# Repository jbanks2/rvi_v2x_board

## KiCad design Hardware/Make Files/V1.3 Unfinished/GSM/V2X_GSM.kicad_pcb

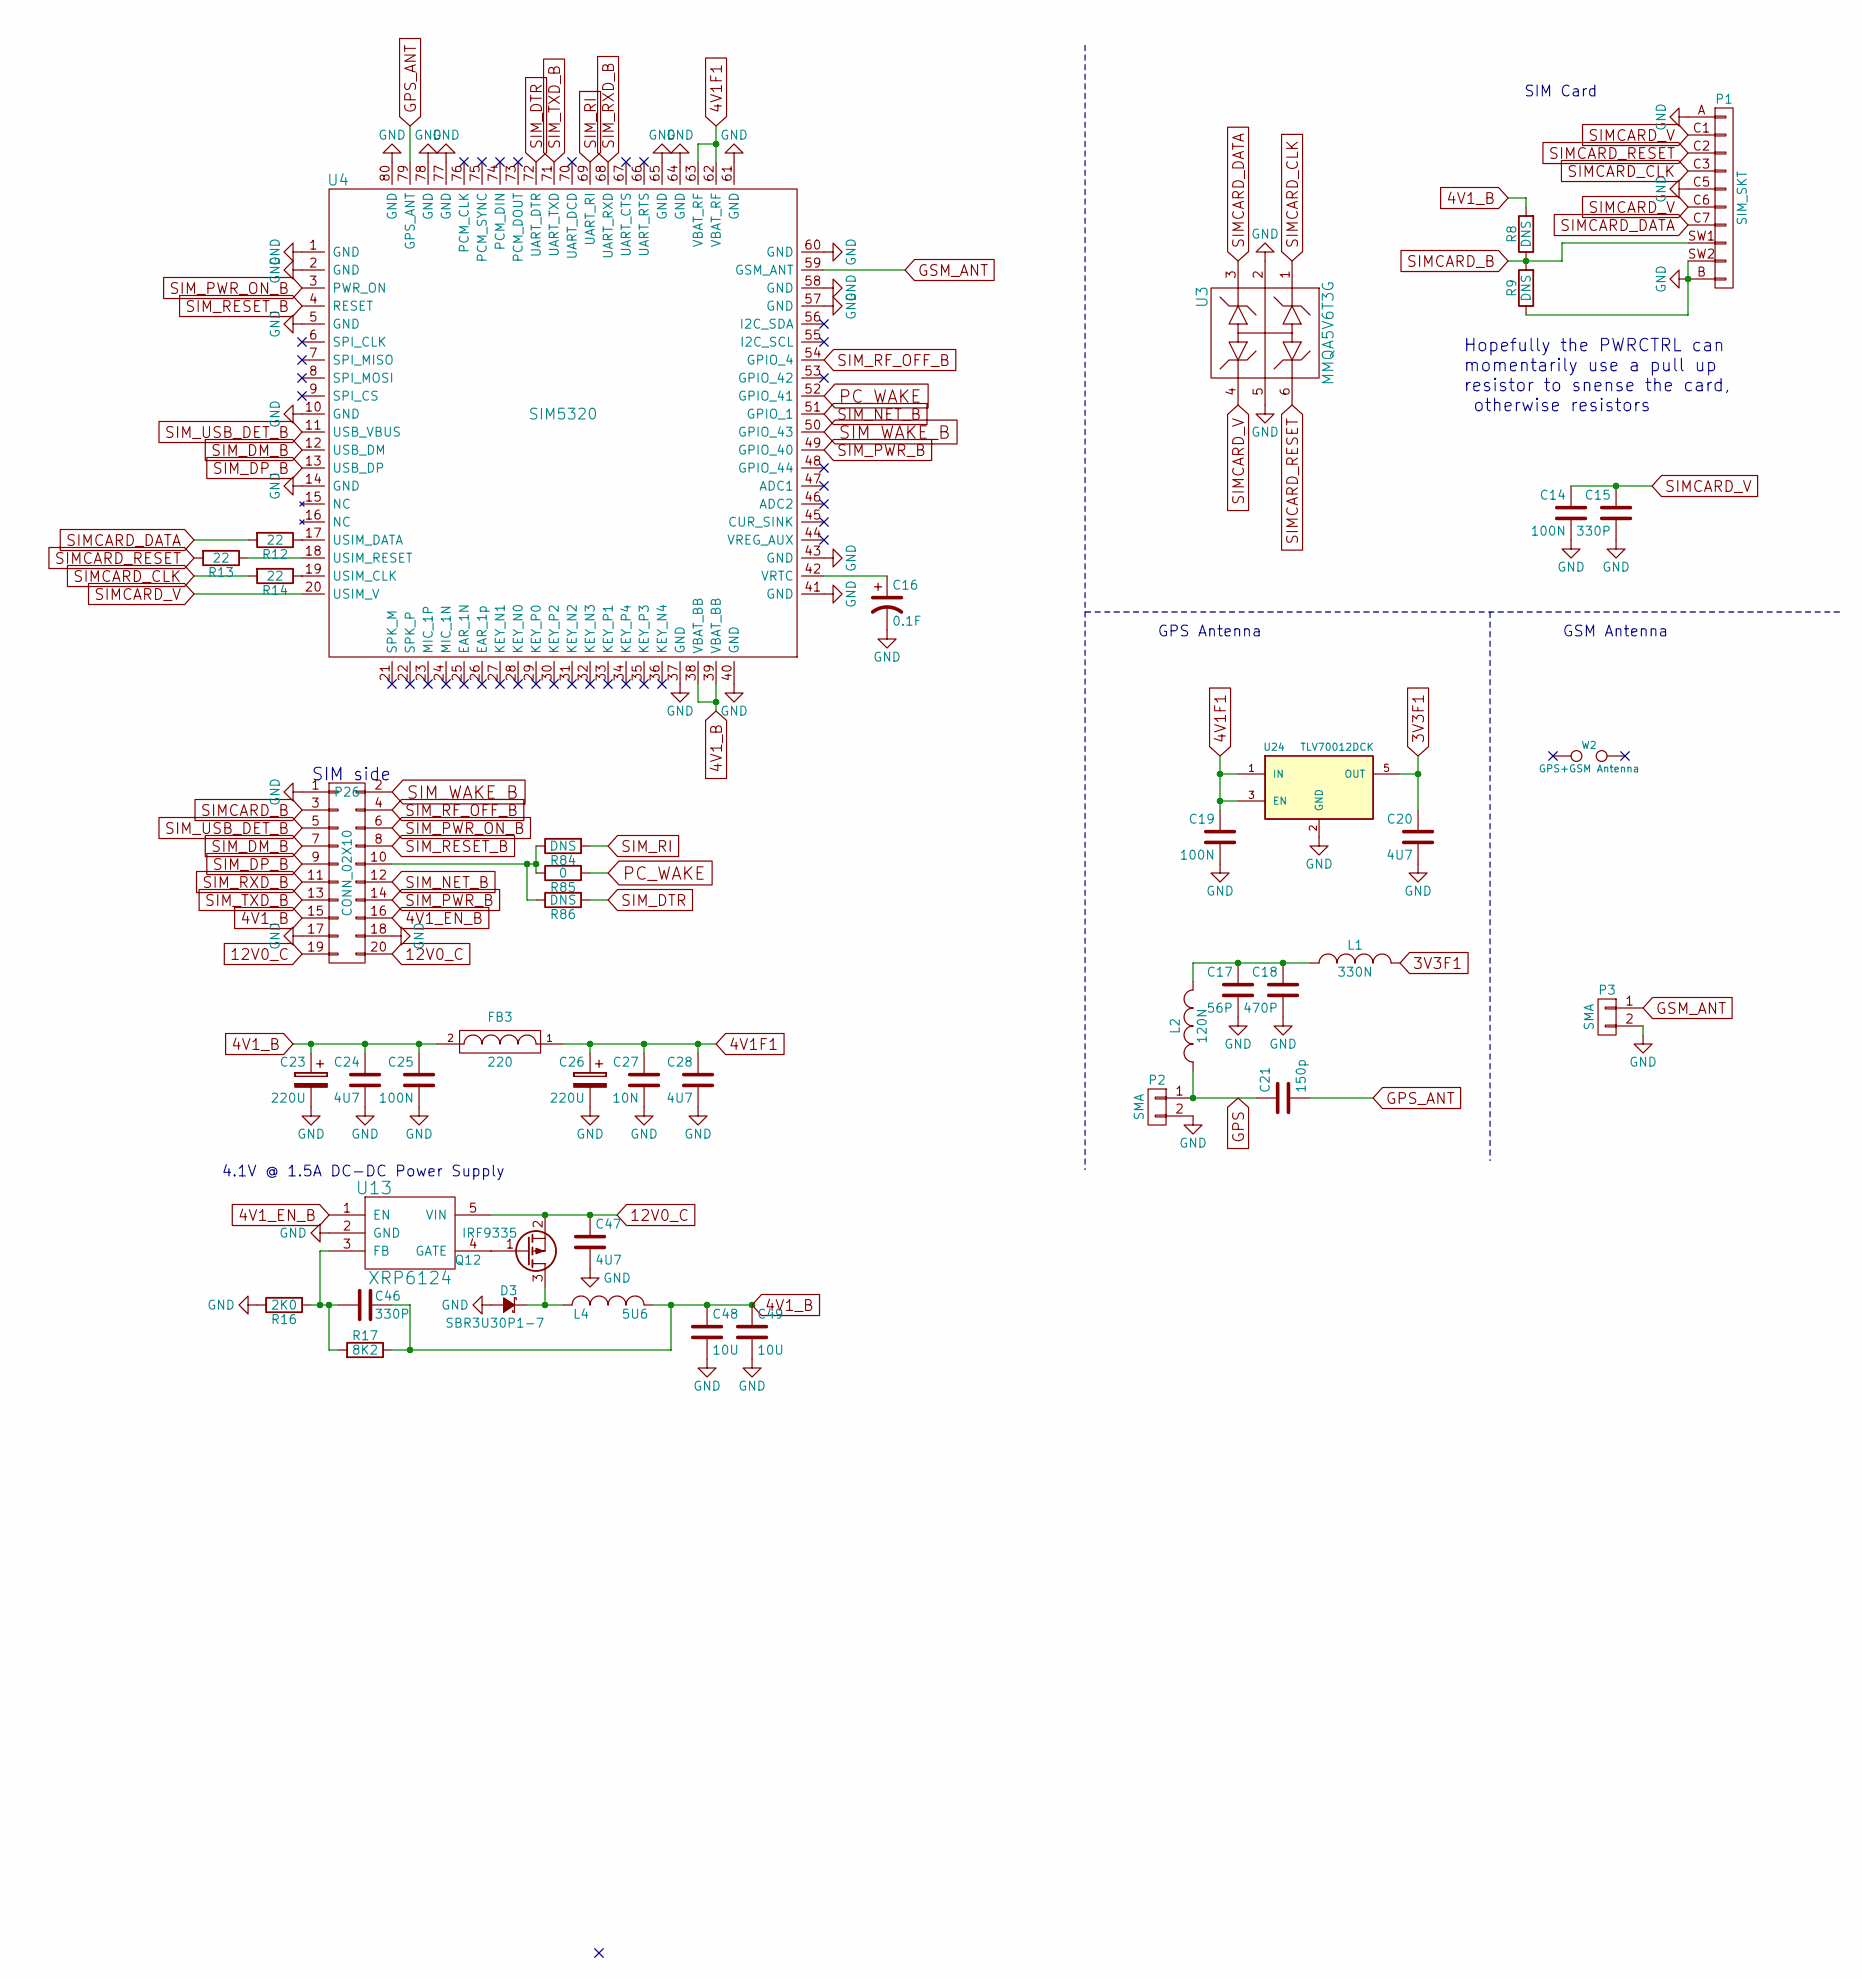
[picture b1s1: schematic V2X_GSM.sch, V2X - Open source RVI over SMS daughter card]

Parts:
C14, C19, C25: 100N; C_0603_SM
C15, C46: 330P; C_0603_SM
C16: 0.1F; C_Radial_D12.5_L25_P5; Mouser PN 504-KR-5R5C104-R
C17: 56P; C_0603_SM
C18: 470P; C_0603_SM
C20, C24, C28, C47: 4U7; C_0805_SM
C21: 150p; C_0603_SM
C23, C26: 220U; c_elec_6.3x5.8
C27: 10N; C_0603_SM
C48, C49: 10U; C_1206_SM
D3: SBR3U30P1-7; SOD-123
FB3: 220; R_0603_sm
L1: 330N; C_0603_SM
L2: 120N; C_0603_SM
L4: 5U6; 4.5x4.5mm_Ind
P1: SIM_SKT; 47553-1001
P2, P3: SMA; SMA-RA_142-0701-801
P26: CONN_02X10; FFC-1MMx20
Q12: IRF9335; SOIC-8_MOS
R8, R9, R84, R86: DNS; R_0603_sm
R12, R13, R14: 22; R_0603_sm
R16: 2K0; R_0603_sm
R17: 8K2; R_0603_sm
R85: 0; R_0603_sm
U3: MMQA5V6T3G; SOT-23-6
U4: SIM5320
U13: XRP6124; SOT-23-5
U24: TLV70012DCK; SOT-23-5
W2: GPS+GSM Antenna

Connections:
3V3F1: C20.1, L1.1, U24.5 (OUT)
4V1F1: C19.1, C26.1, C27.1, C28.1, FB3.1, U4.62 (VBAT_RF), U4.63 (VBAT_RF), U24.1 (IN), U24.3 (EN)
4V1_B: C23.1, C24.1, C25.1, C46.1, C48.1, C49.1, FB3.2, L4.2, P26.15, R8.2, R17.1, U4.38 (VBAT_BB), U4.39 (VBAT_BB)
4V1_EN_B: P26.16, U13.1 (EN)
12V0_C: C47.1, P26.19, P26.20, Q12.2 (S), U13.5 (VIN)
GND: C14.2, C15.2, C16.2, C17.2, C18.2, C19.2, C20.2, C23.2, C24.2, C25.2, C26.2, C27.2, C28.2, C47.2, C48.2, C49.2, D3.2 (A), P1.A, P1.B, P1.C5, P1.SW2, P2.2, P3.2, P26.1, P26.17, P26.18, R9.1, R16.1, U3.2 (K), U3.5 (K2), U4.1 (GND), U4.2 (GND), U4.5 (GND), U4.10 (GND), U4.14 (GND), U4.37 (GND), U4.40 (GND), U4.41 (GND), U4.43 (GND), U4.57 (GND), U4.58 (GND), U4.60 (GND), U4.61 (GND), U4.64 (GND), U4.65 (GND), U4.77 (GND), U4.78 (GND), U4.80 (GND), U13.2 (GND), U24.2 (GND)
GPS: C21.1, L2.1, P2.1
GPS_ANT: C21.2, U4.79 (GPS_ANT)
GSM_ANT: P3.1, U4.59 (GSM_ANT)
unnamed: C16.1, U4.42 (VRTC)
unnamed: C17.1, C18.1, L1.2, L2.2
unnamed: C46.2, R16.2, R17.2, U13.3 (FB)
unnamed: D3.1 (K), L4.1, Q12.3 (D)
unnamed: P26.10, R84.1, R85.1, R86.1
unnamed: Q12.1 (G), U13.4 (GATE)
unnamed: R12.1, U4.17 (USIM_DATA)
unnamed: R13.1, U4.18 (USIM_RESET)
unnamed: R14.1, U4.19 (USIM_CLK)
PC_WAKE: R85.2, U4.52 (GPIO_41)
SIMCARD_B: P1.SW1, P26.3, R8.1, R9.2
SIMCARD_CLK: P1.C3, R14.2, U3.1 (A1)
SIMCARD_DATA: P1.C7, R12.2, U3.3 (A2)
SIMCARD_RESET: P1.C2, R13.2, U3.6 (A4)
SIMCARD_V: C14.1, C15.1, P1.C1, P1.C6, U3.4 (A4), U4.20 (USIM_V)
SIM_DM_B: P26.7, U4.12 (USB_DM)
SIM_DP_B: P26.9, U4.13 (USB_DP)
SIM_DTR: R86.2, U4.72 (UART_DTR)
SIM_NET_B: P26.12, U4.51 (GPIO_1)
SIM_PWR_B: P26.14, U4.49 (GPIO_40)
SIM_PWR_ON_B: P26.6, U4.3 (PWR_ON)
SIM_RESET_B: P26.8, U4.4 (RESET)
SIM_RF_OFF_B: P26.4, U4.54 (GPIO_4)
SIM_RI: R84.2, U4.69 (UART_RI)
SIM_RXD_B: P26.11, U4.68 (UART_RXD)
SIM_TXD_B: P26.13, U4.71 (UART_TXD)
SIM_USB_DET_B: P26.5, U4.11 (USB_VBUS)
SIM_WAKE_B: P26.2, U4.50 (GPIO_43)

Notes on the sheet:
SIM Card
GPS Antenna
GSM Antenna
Hopefully the PWRCTRL can momentarily use a pull up resistor to snense the card, otherwise resistors
SIM side
4.1V @ 1.5A DC-DC Power Supply

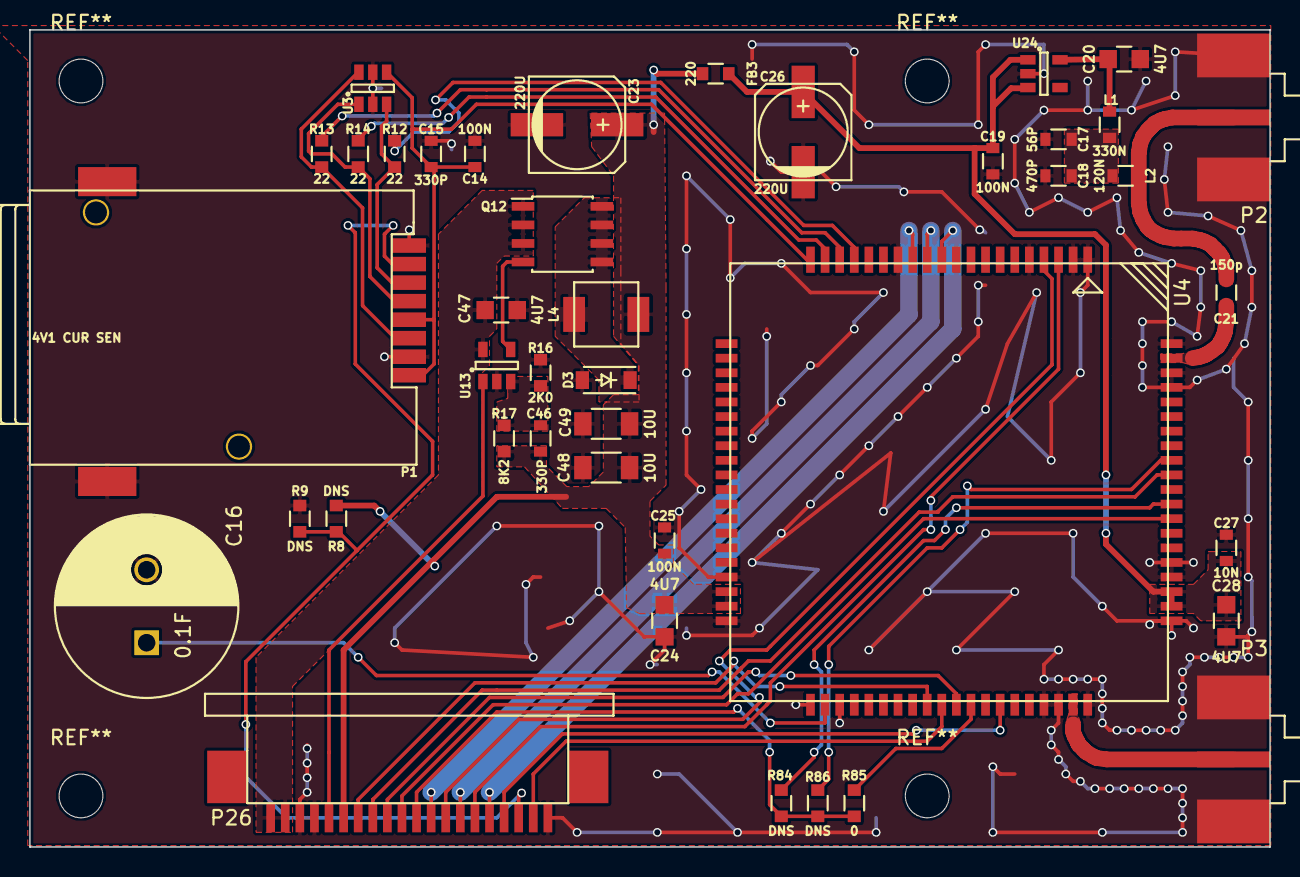
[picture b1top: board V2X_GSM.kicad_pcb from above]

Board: 2 copper layers, 85.0 x 56.0 mm, 42 parts (0 on the bottom side), 37 nets.

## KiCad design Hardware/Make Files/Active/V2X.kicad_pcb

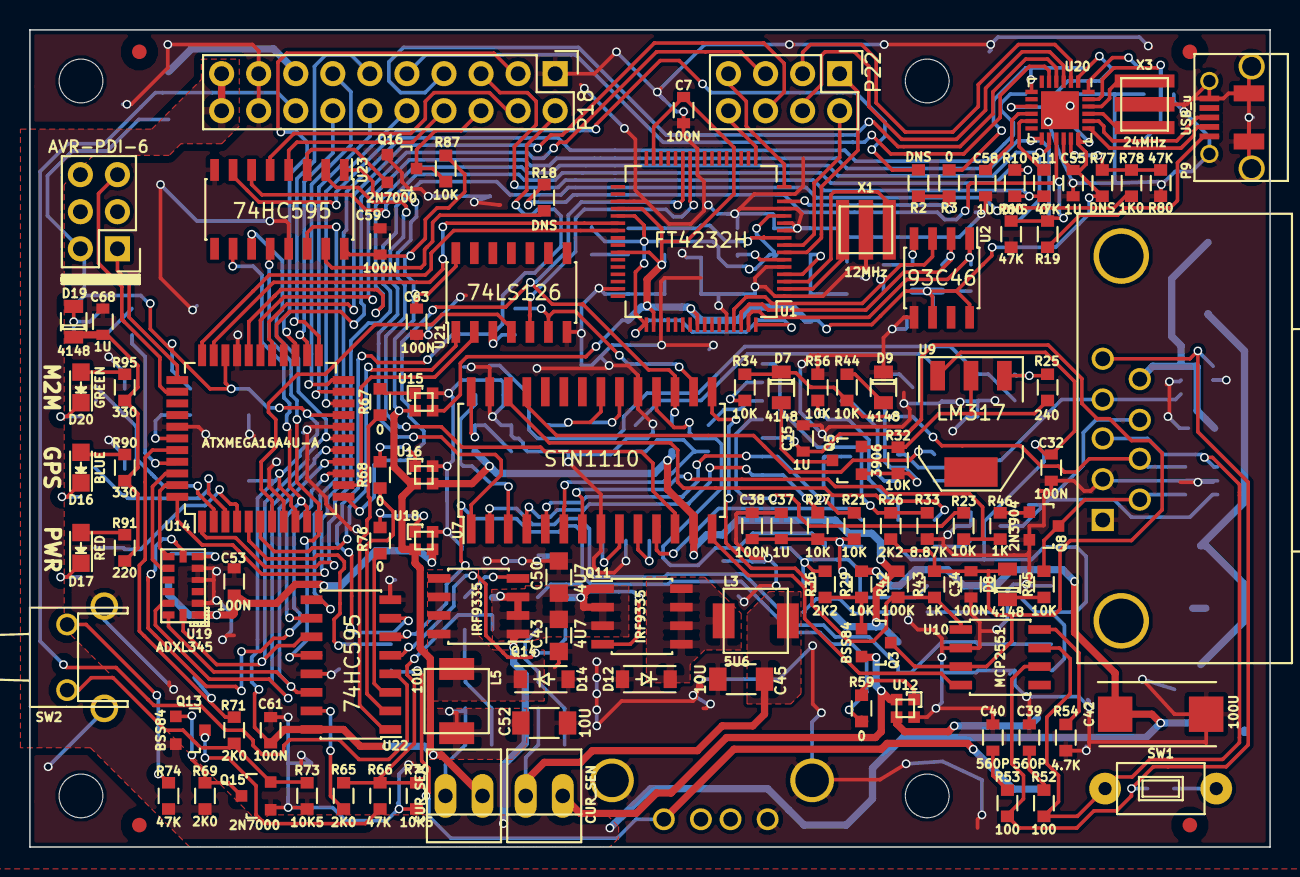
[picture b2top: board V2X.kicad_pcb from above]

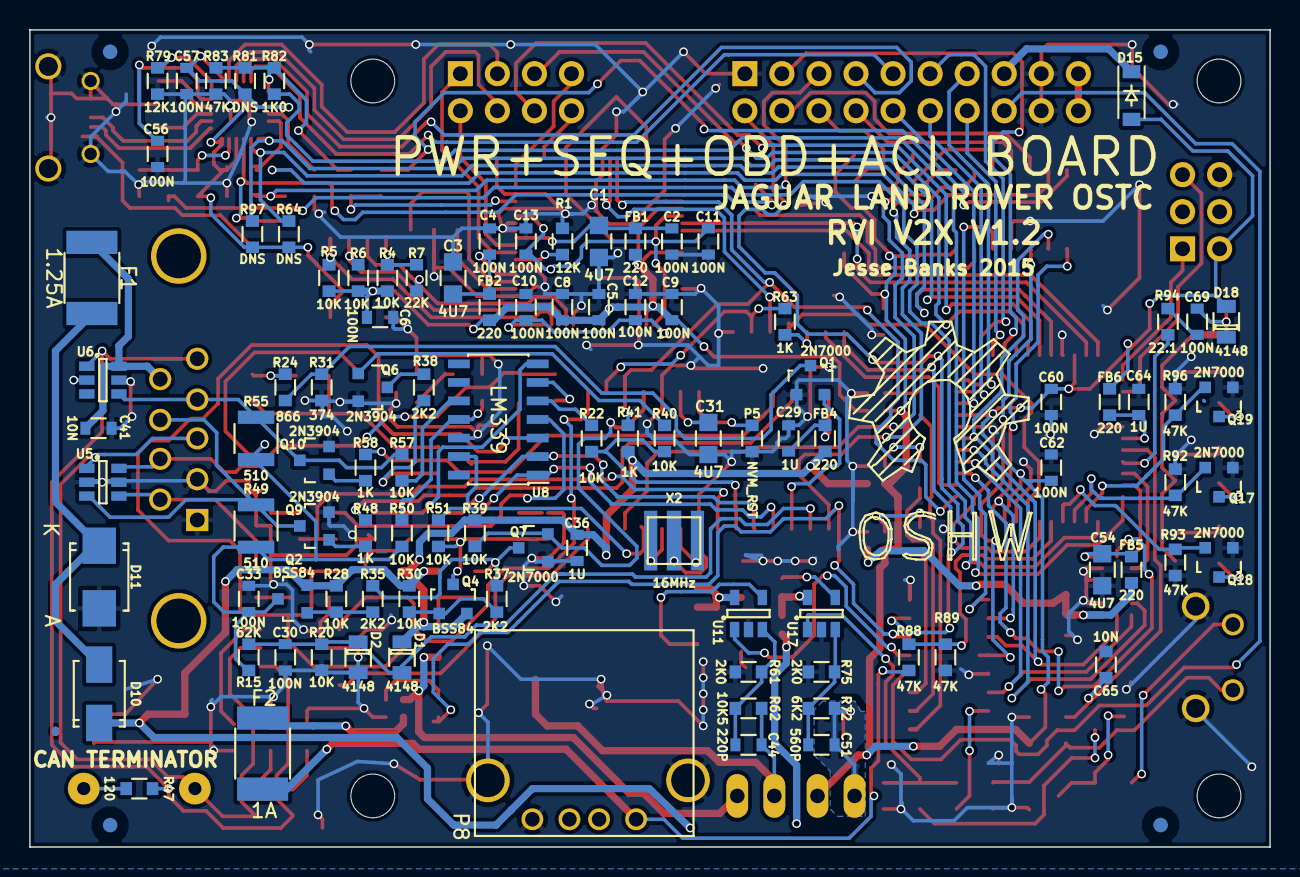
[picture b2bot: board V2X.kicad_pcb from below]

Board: 2 copper layers, 85.0 x 56.0 mm, 223 parts (106 on the bottom side), 179 nets.

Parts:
C1, C3, C31, C43, C50, C54: 4U7; C_0805_SM
C2, C4, C5, C6, C7, C8, C9, C10, C11, C12, C13, C30, C32, C33, C34, C38, C53, C56, C57, C59, C60, C61, C62, C63, C69: 100N; C_0603_SM
C29, C35, C36, C37, C55, C58, C64, C68: 1U; C_0603_SM
C39, C40, C51: 560P; C_0603_SM
C41: 10N; C_0603_SM
C42: 100U; TantalC_SizeD_EIA-7343_Reflow
C44: 220P; C_0603_SM
C45, C52: 10U; C_1206_SM
C65: 10N; R_0603_sm
CON1: AVR-PDI-6; Pin_Header_Straight_2x03
D1, D2, D7, D8, D9, D18, D19: 4148; Diode_0805_12_SM
D10: B320A-13-F; SMA_Standard
D11: SMBJ16A; SMB_Standard
D12, D14: SBR3U30P1-7; SOD-123
D15: MMSZ4678T1G; SOD-123
D16: BLUE; LED-0805-SM
D17: RED; LED-0805-SM
D20: GREEN; LED-0805-SM
F1: 1.25A; R_1812
F2: 1A; R_1812
FB1, FB2, FB4, FB5, FB6: 220; R_0603_sm
J1: DB9; D09P13B4PA00LF
L3: 5U6; 4.5x4.5mm_Ind
L5: 10U; 4.5x4.5mm_Ind
P5: NVM_RST; R_0603_sm
P6: Board Mount 1; MountingHole_3mm
P7: Ficudial1; Fiducial_1mm_Dia_2.54mm_Outer_CopperTop
P8: USB_A
P9: USB_u; USB_Micro-B-DX4R005JJ2R1800
P10: Board Mount 2; MountingHole_3mm
P11: Ficudial2; Fiducial_1mm_Dia_2.54mm_Outer_CopperTop
P12: Board Mount 3; MountingHole_3mm
P13: Ficudial3; Fiducial_1mm_Dia_2.54mm_Outer_CopperTop
P15: Board Mount 4; MountingHole_3mm
P16: Ficudial4; Fiducial_1mm_Dia_2.54mm_Outer_CopperTop
P17, P19: CUR_SEN; PINHEAD1-2
P18: CONN_02X08; Pin_Header_Straight_2x10
P20: Jumper 1; Fiducial_1mm_Dia_2.54mm_Outer_CopperTop
P21: Jumper 2; Fiducial_1mm_Dia_2.54mm_Outer_CopperTop
P22: CONN_02X04; Pin_Header_Straight_2x04
P23: Jumper 3; Fiducial_1mm_Dia_2.54mm_Outer_CopperTop
P24: Jumper 4; Fiducial_1mm_Dia_2.54mm_Outer_CopperTop
Q1, Q7, Q15, Q16, Q17, Q18, Q19: 2N7000; SOT_23_123
Q2, Q3, Q4, Q13: BSS84; SOT_23_123
Q5: 3906; SOT_23_123
Q6, Q8, Q9, Q10: 2N3904; SOT_23_123
Q11, Q14: IRF9335; SOIC-8_MOS
R1, R79: 12K; R_0603_sm
R2, R10, R18, R64, R77, R81, R97: DNS; R_0603_sm
R3, R11, R59, R67, R68, R76: 0; R_0603_sm
R4, R5, R6, R20, R21, R22, R23, R27, R28, R29, R30, R32, R34, R39, R40, R44, R45, R50, R51, R56, R57, R87: 10K; R_0603_sm
R7: 22K; R_0603_sm
R15: 62K; R_0603_sm
R19, R60, R66, R74, R80, R83, R88, R89, R92, R93, R96: 47K; R_0603_sm
R24: 866; R_0603_sm
R25: 240; R_0603_sm
R26, R35, R36, R37, R38: 2K2; R_0603_sm
R31: 374; R_0603_sm
R33: 8.87K; R_0603_sm
R41, R43, R46, R48, R58, R63: 1K; R_0603_sm
R42: 100K; R_0603_sm
R47: 120; R_0603_sm
R49, R55: 510; R_1210_SM
R52, R53: 100; R_0603_sm
R54: 4.7K; R_0603_sm
R61, R65, R69, R71, R75: 2K0; R_0603_sm
R62, R70, R73: 10K5; R_0603_sm
R72: 6K2; R_0603_sm
R78, R82: 1K0; R_0603_sm
R90, R95: 330; R_0603_sm
R91: 220; R_0603_sm
R94: 22.1; R_0603_sm
SW1: SPST; SW_SPST_A6TN_TH
SW2: SW_PUSH; PTS645VK58-2-LFS
U1: FT4232H; LQFP-64_10x10mm_Pitch0.5mm
U2: 93C46; SOIC-8_3.9x4.9mm_Pitch1.27mm
U5, U6: ESDAxxSC6; SOT-23-6
U7: STN1110; SOIC-28_7.5x17.9mm_Pitch1.27mm
U8: LM339; SOIC-14_3.9x8.7mm_Pitch1.27mm
U9: LM317; SOT-223
U10: MCP2551; SOIC-8_3.9x4.9mm_Pitch1.27mm
U11, U17: XRP6124; SOT-23-5
U12, U15, U16, U18: SLG59M; STDFN-4
U14: ATXMEGA16A4U-A; TQFP-44_10x10mm_Pitch0.8mm
U19: ADXL345; LGA-14_5x3mm
U20: USB2242; QFN-24-1EP_4x4mm_Pitch0.5mm
U21: 74LS126; SOIC-14_3.9x8.7mm_Pitch1.27mm
U22, U23: 74HC595; SOIC-16_3.9x9.9mm_Pitch1.27mm
X1: 12MHz; AWSCR
X2: 16MHz; AWSCR
X3: 24MHz; AWSCR

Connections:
3V3_A: C59.1, C60.1, C61.1, C62.1, C63.1, CON1.2, D15.2, D18.2, FB6.1, P19.1, R87.2, U14.9, U14.19, U14.31, U15.2, U16.2, U18.2, U21.14, U22.16, U23.16
3V3_B: C5.1, C6.1, C7.1, C8.1, C9.1, C55.1, C57.1, FB1.1, FB2.1, R4.2, R5.1, R6.1, R64.2, R77.2, R81.2, R97.2, U1.20, U1.31, U1.36, U1.42, U1.50, U1.56, U2.6, U2.8, U15.3, U20.1, U20.9, U20.16, U20.18
3V3_B_EN: R67.1, U22.1
3V3_C: C36.1, D1.1, FB4.1, Q4.2, R39.1, R41.1, R42.1, U7.13, U16.3
3V3_C_EN: R68.1, U22.2
3V3_D: C53.1, FB5.1, U18.3, U19.1
3V3_D_EN: R76.1, U22.3
3V3_E: C68.1, D19.1, R90.2, R91.2, R95.2
3V3_EN: R65.1, U22.15
3V3_F: C64.1, FB6.2, U14.39
4V1_A: D15.1, P18.15
4V1_EN: P18.16, U22.4
5V0_A: P17.1, Q3.2, U12.2
5V0_B: F2.1, U12.3
5V0_B_EN: R59.1, U22.6
5V0_B_OUT: F2.2, P8.1, R88.2
5V0_EN: U11.1, U22.5
5V0_HOST: P9.1, R19.1
12V0_A: C41.1, F1.1, J1.9, U6.6
12V0_B: C42.1, C43.1, C50.1, D10.1, P18.19, P18.20, Q2.2, Q11.2, Q13.2, Q14.2, R28.1, R29.1, R30.1, R69.1, R74.1, U11.5, U17.5
ACCEL_RXD: U1.38, U14.32
ACCEL_TXD: U1.39, U14.33
ACL_INT1: U14.43, U19.8
ACL_INT2: U14.42, U19.9
BAT_SAMPLE: C30.1, D1.2, D2.1, R15.2, R20.1, U7.2
BUTTON: C65.2, R71.2, U14.40
CAN_3.3V_SW: C37.1, C38.1, Q4.3, R21.1, R27.1, R51.1
CAN_5V_SW: C34.1, C35.1, D8.2, Q3.3, R26.1, R43.1, U8.3, U10.3
CAN_12V_SW: C32.1, C33.1, Q2.3, R15.1, R49.2, R50.1, R55.2, U9.3
CAN_BUF_FTDI: U14.7, U21.4
CAN_BUF_SEQ: U14.6, U21.1
CAN_CLK: U7.9, X2.1
CAN_CLKN: U7.10, X2.2
CAN_H: J1.3, R52.1, SW1.1, U5.1, U10.7
CAN_L: J1.5, R47.1, R53.1, U6.1, U10.6
CAN_POWERDOWN: Q7.2, R39.2, U7.18
CAN_RX: U7.14, U10.4
CAN_RXD: R63.2, U7.16, U21.6
CAN_RXD_FTDI: U1.26, U21.5
CAN_RXD_SEQ: U14.13, U21.2
CAN_TX: R42.2, R43.2, U7.15, U10.1
CAN_TXD: R41.2, U1.27, U7.17, U14.12
EECLK: R6.2, U1.62, U2.2
EECS: R5.2, U1.63, U2.1
EEDATA: R7.2, U1.61, U2.3
FT1V8: C10.1, C11.1, C12.1, C13.1, U1.12, U1.37, U1.49, U1.64
FT3V3PHY: C3.1, C4.1, FB2.2, U1.4
FT3V3PLL: C1.1, C2.1, FB1.2, U1.9
FTDI_DM: P22.1, U1.7
FTDI_DP: P22.2, U1.8
FT_CLK: U1.2, X1.2
FT_CLKN: U1.3, X1.1
GND: C1.2, C2.2, C3.2, C4.2, C5.2, C6.2, C7.2, C8.2, C9.2, C10.2, C11.2, C12.2, C13.2, C29.2, C30.2, C31.2, C32.2, C33.2, C34.2, C35.2, C36.2, C37.2, C38.2, C39.2, C40.2, C41.2, C42.2, C43.2, C45.2, C50.2, C52.2, C53.2, C54.2, C55.2, C56.2, C57.2, C58.2, C59.2, C60.2, C61.2, C62.2, C63.2, C64.2, C65.1, C68.2, CON1.6, D2.2, D9.1, D11.2, D12.2, D14.2, J1.1, J1.2, P5.2, P8.4, P8.5, P9.5, P9.6, P18.1, P18.17, P18.18, Q1.1, Q6.2, Q7.1, Q8.2, Q9.2, Q10.2, Q15.1, Q16.1, Q17.1, Q18.1, Q19.1, R1.2, R20.2, R31.1, R33.1, R54.2, R56.2, R60.2, R61.1, R70.1, R73.1, R75.2, R79.1, R80.2, R83.1, R89.1, R92.1, R93.1, R96.1, SW2.S, U1.1, U1.5, U1.10, U1.11, U1.13, U1.15, U1.25, U1.35, U1.47, U1.51, U1.60, U2.5, U5.2, U5.5, U6.2, U6.5, U7.8, U7.19, U7.27, U8.12, U10.2, U11.2, U12.4, U14.8, U14.18, U14.30, U14.38, U15.4, U16.4, U17.2, U18.4, U19.2, U19.4, U19.5, U20.25, U21.7, U22.8, U22.13, U23.8, U23.13, X1.3, X2.3, X3.3
HOST_SC: R88.1, R89.2, U14.5
HUB_CLK: U20.22, X3.2
HUB_CLKN: U20.21, X3.1
HUB_DM: P9.2, U20.19
HUB_DP: P9.3, U20.20
HUB_ENABLE: R18.1, U23.15
HUB_PWR_PRT1: R3.1, R81.1, R82.1, R83.2, U20.7
HUB_PWR_PRT2: R11.2, U20.11
HUB_SCL: R64.1, U14.29, U20.14
HUB_SDA: R97.1, U14.28, U20.13
HUB_STATUS: R82.2, U14.44
HUB_SUSP: R78.2, U14.1
HUB_SUSP_IND: R77.1, R78.1, R80.1, U20.17
ISO_K_TX: R58.1, U7.25
ISO_L_TX: R48.1, U7.26
ISO_RX: R51.2, U7.11, U8.13
J1850+: D7.1, J1.7, R34.2, R44.1, U5.6
J1850-: J1.6, Q8.3, R45.2, U5.4
J1850_BUS_+_TX: R22.2, R40.2, U7.6
J1850_BUS_-_TX: R23.2, R46.2, U7.7
K-LINE: J1.4, Q10.3, R55.1, R57.2, U6.4
L-LINE: J1.8, Q9.3, R49.1, U5.3
unnamed: C29.1, FB4.2, U7.28
unnamed: C31.1, U7.20
unnamed: C39.1, R52.2
unnamed: C40.1, R53.2
unnamed: C44.1, C45.1, L3.2, P17.2, R62.2
unnamed: C44.2, R61.2, R62.1, U11.3
unnamed: C51.1, C52.1, L5.2, P19.2, R72.1
unnamed: C51.2, R72.2, R75.1, U17.3
unnamed: C54.1, FB5.2, U19.6
unnamed: C56.1, U20.23
unnamed: C58.1, U20.10
unnamed: C69.1, D18.1, D19.2
unnamed: C69.2, R94.1
unnamed: D7.2, Q5.3
unnamed: D8.1, R45.1
unnamed: D9.2, R44.2
unnamed: D10.2, D11.1, F1.2
unnamed: D12.1, L3.1, Q11.3
unnamed: D14.1, L5.1, Q14.3
unnamed: D16.1, Q17.3
unnamed: D16.2, R90.1
unnamed: D17.1, Q18.3
unnamed: D17.2, R91.1
unnamed: D20.1, Q19.3
unnamed: D20.2, R95.1
unnamed: P5.1, U7.21
unnamed: Q1.3, R24.2, R31.2
unnamed: Q2.1, R28.2, R35.1
unnamed: Q3.1, R29.2, R36.1
unnamed: Q4.1, R30.2, R37.1
unnamed: Q5.1, R32.2, R38.1
unnamed: Q5.2, R25.1, R32.1, U9.2
unnamed: Q6.1, R40.1
unnamed: Q6.3, R38.2
unnamed: Q7.3, R35.2, R36.2, R37.2
unnamed: Q8.1, R46.1
unnamed: Q9.1, R48.2
unnamed: Q10.1, R58.2
unnamed: Q11.1, U11.4
unnamed: Q13.1, Q15.3, R69.2
unnamed: Q13.3, R66.2
unnamed: Q14.1, U17.4
unnamed: Q15.2, R71.1, R73.2, SW2.1
unnamed: R1.1, U1.6
unnamed: R2.1, R3.2, U1.14
unnamed: R4.1, R7.1, U2.4
unnamed: R22.1, U8.5
unnamed: R23.1, U8.4
unnamed: R24.1, R25.2, U9.1
unnamed: R26.2, R33.2, U8.7
unnamed: R34.1, U8.6
unnamed: R47.2, SW1.2
unnamed: R50.2, R56.1, U8.11
unnamed: R54.1, U10.8
unnamed: R57.1, U8.10
unnamed: R59.2, U12.1
unnamed: R63.1, U21.3
unnamed: R65.2, R66.1, R70.2, U17.1
unnamed: R67.2, U15.1
unnamed: R68.2, U16.1
unnamed: R74.2, SW2.2
unnamed: R76.2, U18.1
unnamed: R79.2, U20.24
unnamed: U22.9, U23.14
PDI: CON1.1, U14.34
PWM/~VPW: Q1.2, U7.3
PWM_RX: R21.2, U7.5, U8.2
SEQ_CHGPUMP: R94.2, U14.41
SEQ_LED1: Q19.2, R96.2, U14.2
SEQ_LED2: Q17.2, R92.2, U14.3
SEQ_LED3: Q18.2, R93.2, U14.4
SEQ_MISO: U14.16, U19.12
SEQ_MOSI: U14.15, U19.13, U22.14
SEQ_RESET: CON1.5, U14.35
SEQ_RXD: P22.7, U1.16
SEQ_RXD_DM: P22.5, U14.26
SEQ_SCK: U14.17, U19.14, U22.11, U23.11
SEQ_SS: U14.14, U19.7
SEQ_TXD: P22.8, U1.17
SEQ_TXD_DP: P22.6, U14.27
SEQ_WAKE: P18.10, U14.20
SIMCARD: P18.3, U14.25
SIM_DM: P18.7, U20.4
SIM_DP: P18.9, U20.5
SIM_NET: P18.12, U14.21
SIM_PWR: P18.14, U14.24
SIM_PWR_ON: Q16.2, U23.3
SIM_RF_OFF: P18.4, U23.5
SIM_RXD: P18.11, U14.23
SIM_TXD: P18.13, U14.22
SIM_USB_DET: P18.5, R10.1, R11.1
SIM_VBUS: R10.2, U23.6
SIM_WAKE: P18.2, U22.7
SR_CLEAR: U14.10, U22.10, U23.10
SR_LATCH: U14.11, U22.12, U23.12
USB_INT_DM: P22.3, U20.2
USB_INT_DP: P22.4, U20.3
~CAN_RESET: U7.1, U23.2
~CAN_SLEEP: U7.12, U23.1
~FTDI_RESET: R2.2, U23.7
~HUB_RESET: R18.2, R19.2, R60.1, U20.15
~SIM_PWR_ON: P18.6, Q16.3, R87.1
~SIM_RESET: P18.8, U23.4
~VPW_RX: R27.2, U7.4, U8.1

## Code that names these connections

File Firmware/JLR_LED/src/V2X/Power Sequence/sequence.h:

/*
 * IncFile1.h
 *
 * Created: 10/15/2015 2:48:04 PM
 *  Author: Kevin
 */ 


#ifndef SEQUENCE_H_
#define SEQUENCE_H_

#include "../common/v2xcomm.h"


#define SEQ_MOSI EXT1_PIN_16	//DS
#define SR_LATCH EXT1_PIN_12	//ST_CP
#define SEQ_SCK EXT1_PIN_18		//SH_CP
#define SR_CLEAR EXT1_PIN_11	//MR

#define A 0X8000
#define B 0X4000
#define C 0X2000
#define D 0X1000
#define E 0X0800
#define F 0X0400
#define G 0X0200
#define H 0X0100
#define I 0x0080
#define J 0x0040
#define K 0x0020
#define L 0x0010
#define M 0x0008
#define N 0x0004
#define O 0x0002
#define P 0x0001


typedef struct step {
	uint16_t value;    // output value
	uint16_t interval; // interval in ms
} step_t;

typedef struct power_state {
	uint16_t curr;	//current bit state
} power_state_t;

struct power_state power;

void init_power_seq(void);
void set_register(void);
void bits_To_Shift_Register(uint16_t bits);
void run_sequence(struct step sequence[], int size);
void turn_on (uint16_t pin_name_on);
void turn_off(uint16_t pin_name_off);

static uint16_t state = 0x0000;

#endif /* SEQUENCE_H_ */

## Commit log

2015-09-03 Initial Commit
    Adding project dev files
2015-09-08 Updated visio for next archetecture
2015-09-14 Folder restructuring
    Aligned with CBFW folder structures
2015-09-15 Some changes for V1.1
    Making a backup point, I am planning to rename all the files to
    V2X_xx.xx
2015-09-15 Names changed to V2X
2015-09-15 Update architecture Visio
2015-09-23 Saving V1.1 as archive.
    We are trying a new architecture where the FTDI can be removed. making a
    backup spot
2015-09-24 V1.2 mostly done
    BOM is integrated and creates mouser orders
2015-09-28 V2X v1.2 sch and bom
    Made changes to the schematic to V1.2 (remove FTDI possibly) and
    integrade the BOM information into the sch
2015-10-02 Split V2X in 2 boards, layout of SIM pcb done
2015-10-07 Build pass of main V2X board
    ready to verify
2015-10-08 V1.2 pass complete and ready to order
2015-10-08 Folder cleanup
2015-10-14 Project rework
    Split the Main and GSM boards into separate projects, redesigned Main
    board after flaws were found.
2015-10-16 Added USB-A to design
    discovered the Rpi cannot be back fed over USB, had to add a power Port
2015-10-20 No Rpi Backpower fix
    added a USB-A to the board to power the HOST. fixed LED labeling.
2015-10-21 work from home day
2015-10-21 home to work push
2015-10-22 Verification findings and modifications
2015-10-22 V2X V1.2 PCB build, with shares
2015-10-22 Project ZIP
2015-10-23 BOM updates
2015-10-26 Packaged to order
2015-11-03 V1.2 Ordered
    This is a capture of the project folder at the time f ordering the V1.2
    kit.
2015-11-03 Folder cleanup for next rev
2015-11-04 Project Shares and Next rev cleanup
2015-11-13 Added learnings from V1.2 build
2015-11-13 Added the firmware from UCSD
2015-11-20 got bring-up firmware running
    chip inits and clears the shift register
2015-11-24 functioning build
    board inits and stays on
    USB connects to hub, SIM and FTDI.
    SIM network and power are forwarded to LEDs.
    SIMCARD state is shown on PWR LED
    Charge pump runs for LED's
    FTDI has Rx/Tx path to CAN
2015-11-24 Added Button detection
    created and tested
    bool buttonStatus()
2015-11-25 created buffer and LED macros
2015-12-17 V2X Build learnings
2015-12-17 V2X simple startup sequence
2015-12-23 GSM board update
    new FPC connector, sim5320 moved towards rf connectors
2015-12-23 part of GSM board update
    unsaved files
2015-12-23 small changes to GSM layout
2016-01-29 53200 Updated project shares
2016-01-29 53534 New design verified
2016-01-29 53189 order stuffs
2016-02-02 Sped up sysclk to 32MHz
    NEED more cycles!!!
2016-02-03 ignore update
2016-02-03 dumb
2016-10-20 seems old...
